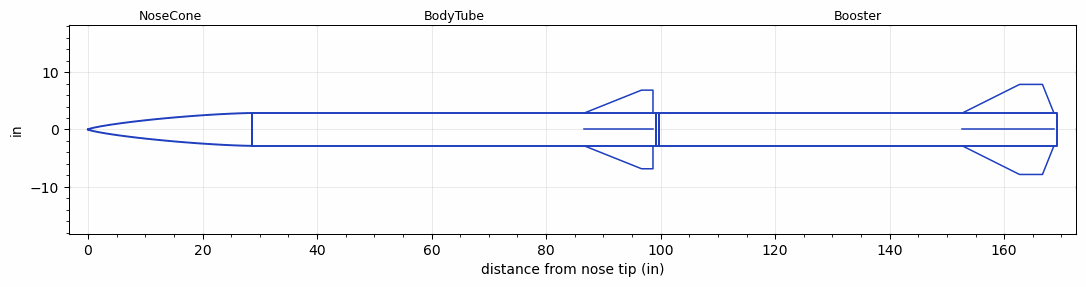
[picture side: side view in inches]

<RASAeroDocument>
 <FileVersion>2</FileVersion>
 <RocketDesign>
  <NoseCone>
   <Length>28.65</Length>
   <Diameter>5.73</Diameter>
   <Shape>Von Karman Ogive</Shape>
   <Location>0</Location>
  </NoseCone>
  <BodyTube>
   <Length>70.51</Length>
   <Diameter>5.73</Diameter>
   <Location>28.65</Location>
   <Fin>
    <Count>4</Count>
    <Chord>12</Chord>
    <Span>4</Span>
    <SweepDistance>10</SweepDistance>
    <TipChord>2</TipChord>
    <Thickness>0.5</Thickness>
    <Location>12.5</Location>
    <AirfoilSection>Hexagonal</AirfoilSection>
    <FX1>1</FX1>
    <FX3>1</FX3>
   </Fin>
  </BodyTube>
  <Booster>
   <Length>69.51</Length>
   <Diameter>5.73</Diameter>
   <InsideDiameter>5.73</InsideDiameter>
   <Location>99.16</Location>
   <ShoulderLength>0.51</ShoulderLength>
   <Fin>
    <Count>4</Count>
    <Chord>16</Chord>
    <Span>5</Span>
    <SweepDistance>10</SweepDistance>
    <TipChord>4</TipChord>
    <Thickness>0.375</Thickness>
    <LERadius>0.1</LERadius>
    <Location>16.5</Location>
    <AirfoilSection>Hexagonal</AirfoilSection>
    <FX1>2</FX1>
    <FX3>2</FX3>
   </Fin>
  </Booster>
  <Surface>Smooth (Zero Roughness)</Surface>
  <ModifiedBarrowman>False</ModifiedBarrowman>
  <Turbulence>False</Turbulence>
  <UseBooster1>False</UseBooster1>
  <UseBooster2>False</UseBooster2>
 </RocketDesign>
 <LaunchSite>
  <Altitude>0</Altitude>
  <Pressure>0</Pressure>
  <RodAngle>0</RodAngle>
  <RodLength>4</RodLength>
  <Temperature>74</Temperature>
  <WindSpeed>0</WindSpeed>
 </LaunchSite>
 <Recovery>
  <Altitude1>1000</Altitude1>
  <Altitude2>1000</Altitude2>
  <DeviceType1>None</DeviceType1>
  <DeviceType2>None</DeviceType2>
  <Event1>False</Event1>
  <Event2>False</Event2>
  <Size1>1</Size1>
  <Size2>1</Size2>
  <EventType1>None</EventType1>
  <EventType2>None</EventType2>
  <CD1>1.33</CD1>
  <CD2>1.33</CD2>
 </Recovery>
 <SimulationList>
  <Simulation>
   <SustainerEngine>N1975-GR  (CTI)</SustainerEngine>
   <SustainerLaunchWt>57</SustainerLaunchWt>
   <SustainerNozzleDiameter>2.5</SustainerNozzleDiameter>
   <SustainerCG>60.99</SustainerCG>
   <SustainerIgnitionDelay>0</SustainerIgnitionDelay>
   <Booster1Engine>O3400-IM-P  (CTI)</Booster1Engine>
   <Booster1LaunchWt>114.23</Booster1LaunchWt>
   <Booster1SeparationDelay>0</Booster1SeparationDelay>
   <Booster1IgnitionDelay>0</Booster1IgnitionDelay>
   <Booster1CG>100.54</Booster1CG>
   <Booster1NozzleDiameter>2.5</Booster1NozzleDiameter>
   <IncludeBooster1>True</IncludeBooster1>
   <Booster2Delay>0</Booster2Delay>
   <IncludeBooster2>False</IncludeBooster2>
   <TimetoApogee>50.07833</TimetoApogee>
   <MaxAltitude>48008.62</MaxAltitude>
   <MaxVelocity>2926.156</MaxVelocity>
  </Simulation>
 </SimulationList>
</RASAeroDocument>
